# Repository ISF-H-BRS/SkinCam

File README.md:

# ISF SkinCam

## Introduction

The objective of the SkinCam project was to implement a camera system for real-time skin detection and face verification using multispectral short-wavelength infrared (SWIR) imaging. It originated from previous research projects carried out at Bonn-Rhein-Sieg University of Applied Sciences, such as [FeGeb](https://www.h-brs.de/de/fegeb) and [Beyond SPAI](https://www.h-brs.de/en/beyond-spai).

Based on the original concepts and designs, a new and improved system was developed, offering higher frame rates and optimized SWIR lighting. It is currently being used in various successor projects in biometrics research, such as [BIOLAB](https://www.h-brs.de/en/isf/biolab).

## Concept

The system is based on a Goldeye G-033 SWIR camera by Allied Vision, combined with a multispectral ring light operating at wavelengths of 1050, 1300 and 1550 nm. By evaluating the absorption ratios at these specific wavelengths, it is possible to identify those pixels which have properties characteristic of human skin using a pre-trained classifier.

## Software

The software developed as part of this project is based on code originally written for the project Beyond SPAI, which itself was based on the FeGeb project but extended the original concept by using three SWIR cameras simultaneously, using relay optics to split the image.

A number of image processing filters were implemented to compensate for imperfections in the relay optics. While these aren't strictly necessary for a single-camera system, they were retained in the SkinCam software anyway.

The implementation uses OpenCL for real-time image processing and skin classification and employs a number of other optimizations in order to achieve a stable frame rate of 40 Hz even on mid- to low-end systems.

In addition to the OpenCL [development headers](https://github.com/KhronosGroup/OpenCL-CLHPP), [Qt6](https://www.qt.io/product/qt6), [FreeImage](https://freeimage.sourceforge.io/), [libIFD](https://github.com/ISF-H-BRS/FaceDetector), [libusb](https://libusb.info/), [libzip](https://libzip.org/) and the [Vimba SDK](https://www.alliedvision.com/en/products/vimba-sdk/) are required to build and run the software. Since the Vimba terms and conditions do not permit end-users to download or use the software, the SkinCam software is by default compiled without support for the Vimba SDK.

The firmware directory contains project files for both the newly developed system, which is based on a STM32 microcontroller, as well as for the original FeGeb system, which was based on an 8-bit AVR microcontroller.

A number of captured test images are provided within the repository that can be used to evaluate the software without having the actual camera system available. A setup file is also provided, containing suitable settings as well as necessary calibration and classification data.

## License

All source code for the software and firmware is licensed under the terms of the GNU General Public License (GPLv3). All schematics, layout and CAD files are licensed under the terms of the Creative Commons Attribution-ShareAlike International Public License (CC BY-SA). See COPYING in the respective subdirectories for details.

## Further Information

This document will be expanded over time to further detail some of the underlying concepts. For the time being, detailed information on the original project and concepts can be found in Holger Steiner's PhD thesis, available online [here](http://www.grk1564.uni-siegen.de/publicationPDFbyID?ID=825).

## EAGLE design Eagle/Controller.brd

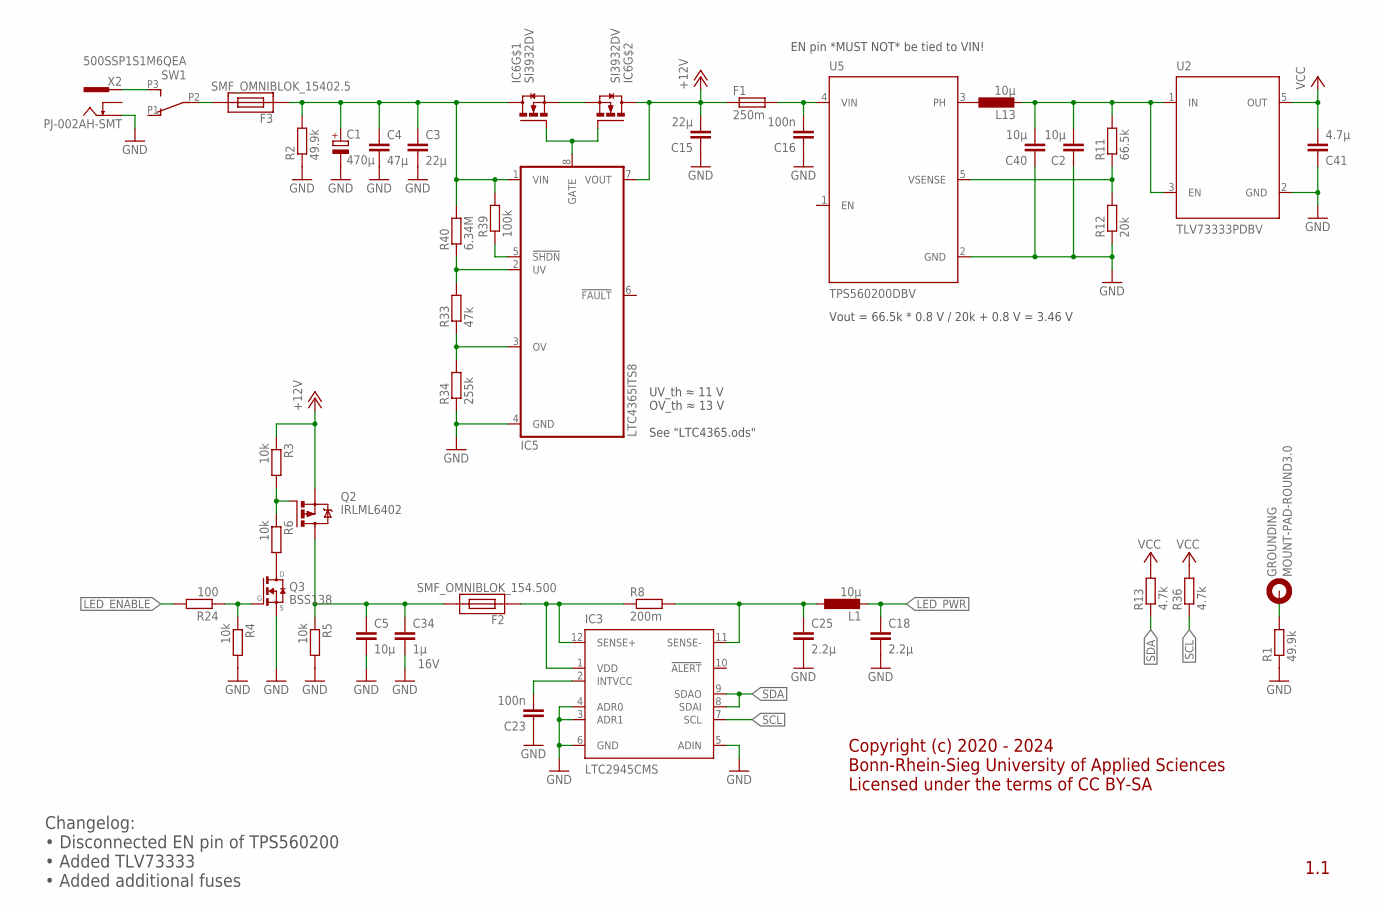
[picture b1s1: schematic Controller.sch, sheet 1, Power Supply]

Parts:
C1: 470µ; UD-10X10_NICHICON
C2, C5, C40: 10µ; C0805
C3: 22µ; C1206
C4: 47µ; C1206
C15: 22µ; C0805
C16, C23: 100n; C0603
C18, C25: 2.2µ; C0805
C34: 1µ; C0805; RATING 16V
C41: 4.7µ; C0805
F1: 250m; R0603
F2: SMF_OMNIBLOK_154.500; NANO2_SMF_FUSEBLOCK
F3: SMF_OMNIBLOK_15402.5; NANO2_SMF_FUSEBLOCK
GROUNDING: MOUNT-PAD-ROUND3.0; 3,0-PAD
IC3: LTC2945CMS; MSOP12
IC5: LTC4365ITS8; TSOT-23-8
IC6: SI3932DV; TSOT-23-6
L1: 10µ; SMD
L13: 10µ; 2SMD
Q2: IRLML6402; MICRO3
Q3: BSS138; SOT23
R1: 49.9k; R0805
R2: 49.9k; R1206
R3, R4, R6: 10k; R0603
R5: 10k; R1206
R8: 200m; R2512
R11: 66.5k; R0603
R12: 20k; R0603
R13, R36: 4.7k; R0603
R24: 100; R0603
R33: 47k; R0603
R34: 255k; R0603
R39: 100k; R0603
R40: 6.34M; R0603
SW1: 500SSP1S1M6QEA
U2: TLV73333PDBV; SOT-23
U5: TPS560200DBV; SOT-23
X2: PJ-002AH-SMT

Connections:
+12V: C15.2, F1.1, IC5.7 (VOUT), IC6.4 (D), Q2.2 (S), R3.1; also elsewhere on the board
GND: C1.-, C2.1, C3.2, C4.2, C5.2, C15.1, C16.1, C18.2, C23.1, C25.2, C34.2, C40.1, C41.1, IC3.3 (ADR1), IC3.4 (ADR0), IC3.5 (ADIN), IC3.6 (GND), IC5.4 (GND), Q3.2 (S), R1.1, R2.1, R4.2, R5.2, R12.1, R34.1, U2.2 (GND), U5.2 (GND), X2.2 (OUT); also elsewhere on the board
LED_ENABLE: R24.2; also elsewhere on the board
LED_PWR: C18.1, L1.2; also elsewhere on the board
unnamed: GROUNDING.B3,0, R1.2
unnamed: C2.2, C40.2, L13.P$2 (2), R11.2, U2.1 (IN), U2.3 (EN)
unnamed: C25.1, IC3.11 (SENSE-), L1.1, R8.2
unnamed: C16.2, F1.2, U5.4 (VIN)
unnamed: Q2.1 (G), R3.2, R6.1
unnamed: Q3.1 (G), R4.1, R24.1
unnamed: Q3.3 (D), R6.2
unnamed: C5.1, C34.1, F2.2, Q2.3 (D), R5.1
unnamed: SW1.P3 (3), X2.1-1 (IN), X2.1-2 (IN)
unnamed: L13.P$1 (1), U5.3 (PH)
unnamed: C1.+, C3.1, C4.1, F3.1, IC5.1 (VIN), IC6.6 (D), R2.2, R39.2, R40.2
unnamed: R11.1, R12.2, U5.5 (VSENSE)
unnamed: F2.1, IC3.1 (VDD), IC3.12 (SENSE+), R8.1
unnamed: F3.2, SW1.P2 (2)
unnamed: IC5.8 (GATE), IC6.1 (G), IC6.3 (G)
unnamed: IC5.3 (OV), R33.1, R34.2
unnamed: IC5.2 (UV), R33.2, R40.1
unnamed: IC5.5 (!SHDN), R39.1
unnamed: IC6.2 (S), IC6.5 (S)
unnamed: C23.2, IC3.2 (INTVCC)
SCL: IC3.7 (SCL), R36.1; also elsewhere on the board
SDA: IC3.8 (SDAI), IC3.9 (SDAO), R13.1; also elsewhere on the board
VCC: C41.2, R13.2, R36.2, U2.5 (OUT); also elsewhere on the board

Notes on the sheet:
Vout = 66.5k * 0.8 V / 20k + 0.8 V = 3.46 V
UV_th ≈ 11 V OV_th ≈ 13 V See "LTC4365.ods"
1.1
EN pin *MUST NOT* be tied to VIN!
Changelog: • Disconnected EN pin of TPS560200 • Added TLV73333 • Added additional fuses
Copyright (c) 2020 - 2024 Bonn-Rhein-Sieg University of Applied Sciences Licensed under the terms of CC BY-SA

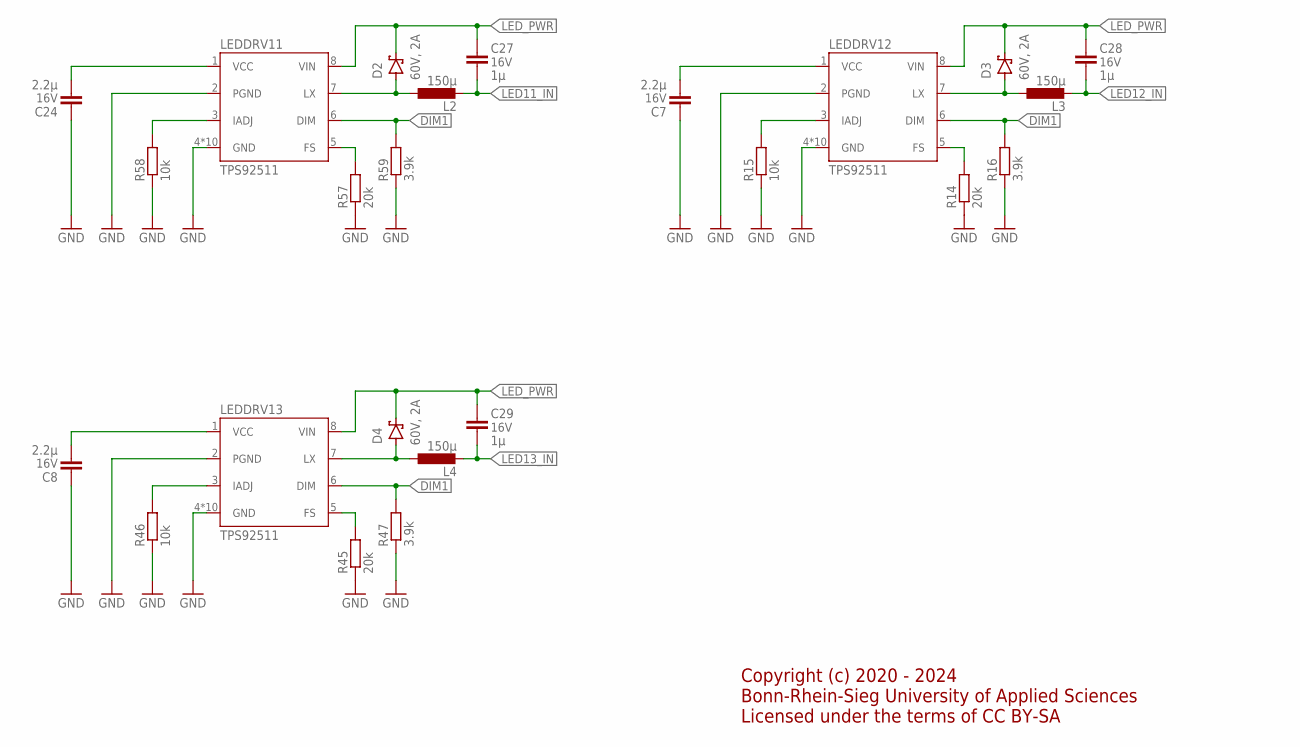
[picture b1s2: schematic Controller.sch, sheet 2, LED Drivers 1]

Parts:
C7, C8, C24: 2.2µ; C0603; RATING 16V
C27, C28, C29: 1µ; C0805; RATING 16V
D2, D3, D4: 60V, 2A; SMB
L2, L3, L4: 150µ; SMD
LEDDRV11, LEDDRV12, LEDDRV13: TPS92511; SOIC-8-EP
R14, R45, R57: 20k; R0603
R15, R46, R58: 10k; R0603
R16, R47, R59: 3.9k; R0603

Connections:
DIM1: LEDDRV11.6 (DIM), LEDDRV12.6 (DIM), LEDDRV13.6 (DIM), R16.2, R47.2, R59.2; also elsewhere on the board
GND: C7.1, C8.1, C24.1, LEDDRV11.2 (PGND), LEDDRV11.4 (GND), LEDDRV11.EPAD (GND), LEDDRV11.P$1 (GND), LEDDRV11.P$2 (GND), LEDDRV11.P$3 (GND), LEDDRV11.P$4 (GND), LEDDRV11.P$5 (GND), LEDDRV11.P$6 (GND), LEDDRV11.P$7 (GND), LEDDRV11.P$8 (GND), LEDDRV12.2 (PGND), LEDDRV12.4 (GND), LEDDRV12.EPAD (GND), LEDDRV12.P$1 (GND), LEDDRV12.P$2 (GND), LEDDRV12.P$3 (GND), LEDDRV12.P$4 (GND), LEDDRV12.P$5 (GND), LEDDRV12.P$6 (GND), LEDDRV12.P$7 (GND), LEDDRV12.P$8 (GND), LEDDRV13.2 (PGND), LEDDRV13.4 (GND), LEDDRV13.EPAD (GND), LEDDRV13.P$1 (GND), LEDDRV13.P$2 (GND), LEDDRV13.P$3 (GND), LEDDRV13.P$4 (GND), LEDDRV13.P$5 (GND), LEDDRV13.P$6 (GND), LEDDRV13.P$7 (GND), LEDDRV13.P$8 (GND), R14.1, R15.1, R16.1, R45.1, R46.1, R47.1, R57.1, R58.1, R59.1; also elsewhere on the board
LED11_IN: C27.2, L2.2; also elsewhere on the board
LED12_IN: C28.2, L3.2; also elsewhere on the board
LED13_IN: C29.2, L4.2; also elsewhere on the board
LED_PWR: C27.1, C28.1, C29.1, D2.C, D3.C, D4.C, LEDDRV11.8 (VIN), LEDDRV12.8 (VIN), LEDDRV13.8 (VIN); also elsewhere on the board
unnamed: D3.A, L3.1, LEDDRV12.7 (LX)
unnamed: LEDDRV12.5 (FS), R14.2
unnamed: LEDDRV12.3 (IADJ), R15.2
unnamed: C7.2, LEDDRV12.1 (VCC)
unnamed: D4.A, L4.1, LEDDRV13.7 (LX)
unnamed: LEDDRV13.5 (FS), R45.2
unnamed: LEDDRV13.3 (IADJ), R46.2
unnamed: C8.2, LEDDRV13.1 (VCC)
unnamed: D2.A, L2.1, LEDDRV11.7 (LX)
unnamed: LEDDRV11.5 (FS), R57.2
unnamed: LEDDRV11.3 (IADJ), R58.2
unnamed: C24.2, LEDDRV11.1 (VCC)

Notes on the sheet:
Copyright (c) 2020 - 2024 Bonn-Rhein-Sieg University of Applied Sciences Licensed under the terms of CC BY-SA

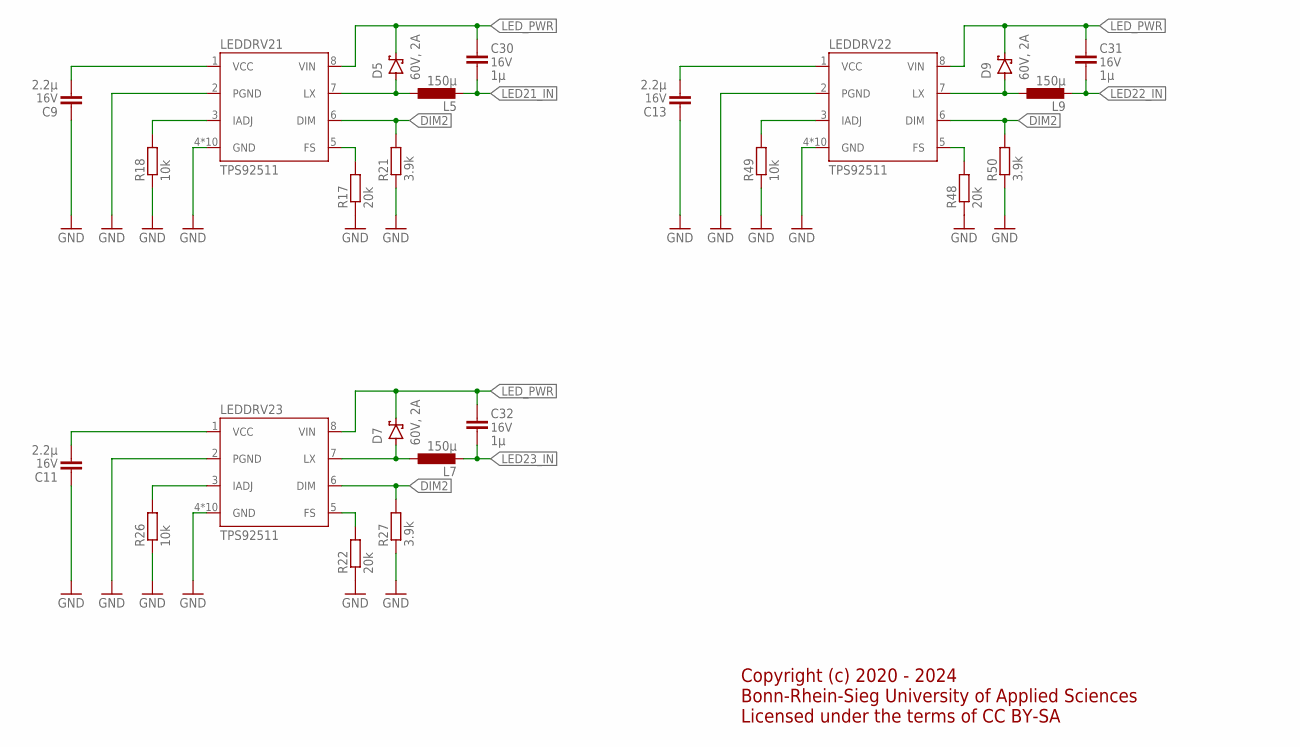
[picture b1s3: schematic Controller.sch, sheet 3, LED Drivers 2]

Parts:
C9, C11, C13: 2.2µ; C0603; RATING 16V
C30, C31, C32: 1µ; C0805; RATING 16V
D5, D7, D9: 60V, 2A; SMB
L5, L7, L9: 150µ; SMD
LEDDRV21, LEDDRV22, LEDDRV23: TPS92511; SOIC-8-EP
R17, R22, R48: 20k; R0603
R18, R26, R49: 10k; R0603
R21, R27, R50: 3.9k; R0603

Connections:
DIM2: LEDDRV21.6 (DIM), LEDDRV22.6 (DIM), LEDDRV23.6 (DIM), R21.2, R27.2, R50.2; also elsewhere on the board
GND: C9.1, C11.1, C13.1, LEDDRV21.2 (PGND), LEDDRV21.4 (GND), LEDDRV21.EPAD (GND), LEDDRV21.P$1 (GND), LEDDRV21.P$2 (GND), LEDDRV21.P$3 (GND), LEDDRV21.P$4 (GND), LEDDRV21.P$5 (GND), LEDDRV21.P$6 (GND), LEDDRV21.P$7 (GND), LEDDRV21.P$8 (GND), LEDDRV22.2 (PGND), LEDDRV22.4 (GND), LEDDRV22.EPAD (GND), LEDDRV22.P$1 (GND), LEDDRV22.P$2 (GND), LEDDRV22.P$3 (GND), LEDDRV22.P$4 (GND), LEDDRV22.P$5 (GND), LEDDRV22.P$6 (GND), LEDDRV22.P$7 (GND), LEDDRV22.P$8 (GND), LEDDRV23.2 (PGND), LEDDRV23.4 (GND), LEDDRV23.EPAD (GND), LEDDRV23.P$1 (GND), LEDDRV23.P$2 (GND), LEDDRV23.P$3 (GND), LEDDRV23.P$4 (GND), LEDDRV23.P$5 (GND), LEDDRV23.P$6 (GND), LEDDRV23.P$7 (GND), LEDDRV23.P$8 (GND), R17.1, R18.1, R21.1, R22.1, R26.1, R27.1, R48.1, R49.1, R50.1; also elsewhere on the board
LED21_IN: C30.2, L5.2; also elsewhere on the board
LED22_IN: C31.2, L9.2; also elsewhere on the board
LED23_IN: C32.2, L7.2; also elsewhere on the board
LED_PWR: C30.1, C31.1, C32.1, D5.C, D7.C, D9.C, LEDDRV21.8 (VIN), LEDDRV22.8 (VIN), LEDDRV23.8 (VIN); also elsewhere on the board
unnamed: D5.A, L5.1, LEDDRV21.7 (LX)
unnamed: LEDDRV21.5 (FS), R17.2
unnamed: LEDDRV21.3 (IADJ), R18.2
unnamed: C9.2, LEDDRV21.1 (VCC)
unnamed: D7.A, L7.1, LEDDRV23.7 (LX)
unnamed: LEDDRV23.5 (FS), R22.2
unnamed: LEDDRV23.3 (IADJ), R26.2
unnamed: C11.2, LEDDRV23.1 (VCC)
unnamed: D9.A, L9.1, LEDDRV22.7 (LX)
unnamed: LEDDRV22.5 (FS), R48.2
unnamed: LEDDRV22.3 (IADJ), R49.2
unnamed: C13.2, LEDDRV22.1 (VCC)

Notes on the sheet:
Copyright (c) 2020 - 2024 Bonn-Rhein-Sieg University of Applied Sciences Licensed under the terms of CC BY-SA

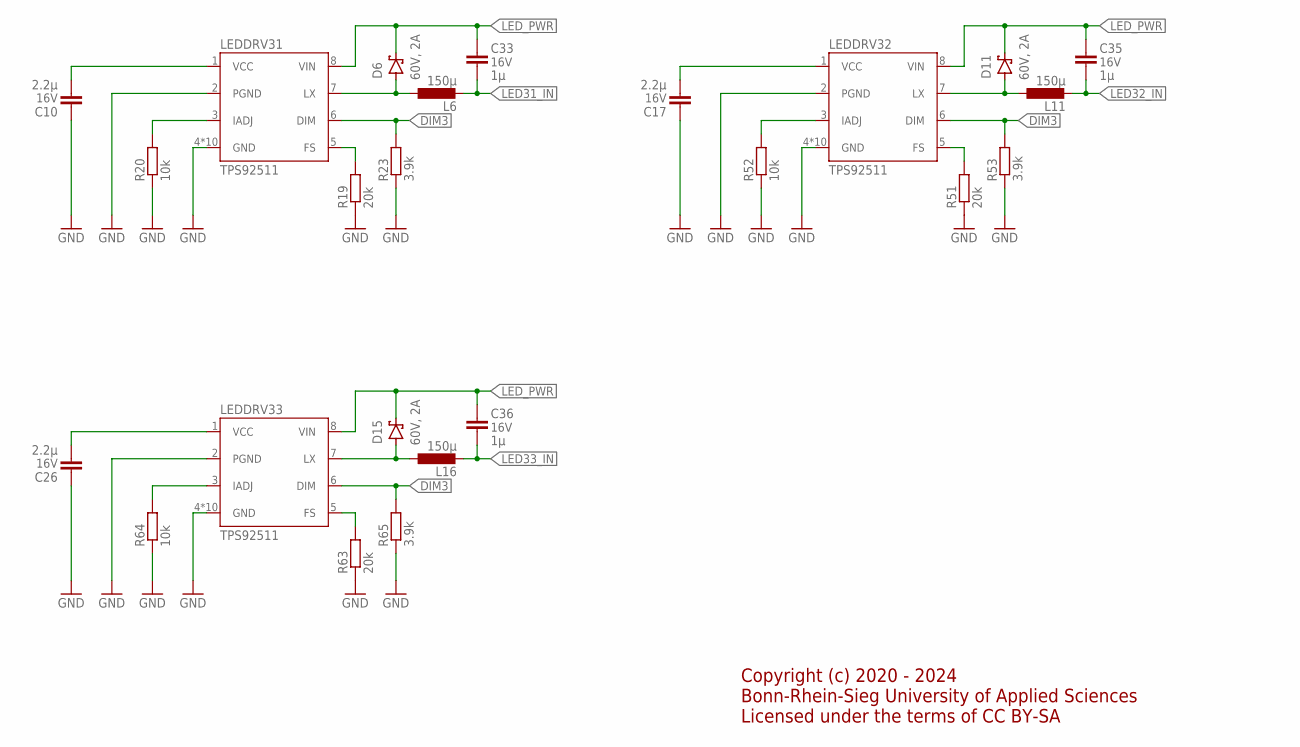
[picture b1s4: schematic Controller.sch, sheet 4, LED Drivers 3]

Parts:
C10, C17, C26: 2.2µ; C0603; RATING 16V
C33, C35, C36: 1µ; C0805; RATING 16V
D6, D11, D15: 60V, 2A; SMB
L6, L11, L16: 150µ; SMD
LEDDRV31, LEDDRV32, LEDDRV33: TPS92511; SOIC-8-EP
R19, R51, R63: 20k; R0603
R20, R52, R64: 10k; R0603
R23, R53, R65: 3.9k; R0603

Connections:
DIM3: LEDDRV31.6 (DIM), LEDDRV32.6 (DIM), LEDDRV33.6 (DIM), R23.2, R53.2, R65.2; also elsewhere on the board
GND: C10.1, C17.1, C26.1, LEDDRV31.2 (PGND), LEDDRV31.4 (GND), LEDDRV31.EPAD (GND), LEDDRV31.P$1 (GND), LEDDRV31.P$2 (GND), LEDDRV31.P$3 (GND), LEDDRV31.P$4 (GND), LEDDRV31.P$5 (GND), LEDDRV31.P$6 (GND), LEDDRV31.P$7 (GND), LEDDRV31.P$8 (GND), LEDDRV32.2 (PGND), LEDDRV32.4 (GND), LEDDRV32.EPAD (GND), LEDDRV32.P$1 (GND), LEDDRV32.P$2 (GND), LEDDRV32.P$3 (GND), LEDDRV32.P$4 (GND), LEDDRV32.P$5 (GND), LEDDRV32.P$6 (GND), LEDDRV32.P$7 (GND), LEDDRV32.P$8 (GND), LEDDRV33.2 (PGND), LEDDRV33.4 (GND), LEDDRV33.EPAD (GND), LEDDRV33.P$1 (GND), LEDDRV33.P$2 (GND), LEDDRV33.P$3 (GND), LEDDRV33.P$4 (GND), LEDDRV33.P$5 (GND), LEDDRV33.P$6 (GND), LEDDRV33.P$7 (GND), LEDDRV33.P$8 (GND), R19.1, R20.1, R23.1, R51.1, R52.1, R53.1, R63.1, R64.1, R65.1; also elsewhere on the board
LED31_IN: C33.2, L6.2; also elsewhere on the board
LED32_IN: C35.2, L11.2; also elsewhere on the board
LED33_IN: C36.2, L16.2; also elsewhere on the board
LED_PWR: C33.1, C35.1, C36.1, D6.C, D11.C, D15.C, LEDDRV31.8 (VIN), LEDDRV32.8 (VIN), LEDDRV33.8 (VIN); also elsewhere on the board
unnamed: D6.A, L6.1, LEDDRV31.7 (LX)
unnamed: LEDDRV31.5 (FS), R19.2
unnamed: LEDDRV31.3 (IADJ), R20.2
unnamed: C10.2, LEDDRV31.1 (VCC)
unnamed: D11.A, L11.1, LEDDRV32.7 (LX)
unnamed: LEDDRV32.5 (FS), R51.2
unnamed: LEDDRV32.3 (IADJ), R52.2
unnamed: C17.2, LEDDRV32.1 (VCC)
unnamed: D15.A, L16.1, LEDDRV33.7 (LX)
unnamed: LEDDRV33.5 (FS), R63.2
unnamed: LEDDRV33.3 (IADJ), R64.2
unnamed: C26.2, LEDDRV33.1 (VCC)

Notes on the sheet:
Copyright (c) 2020 - 2024 Bonn-Rhein-Sieg University of Applied Sciences Licensed under the terms of CC BY-SA

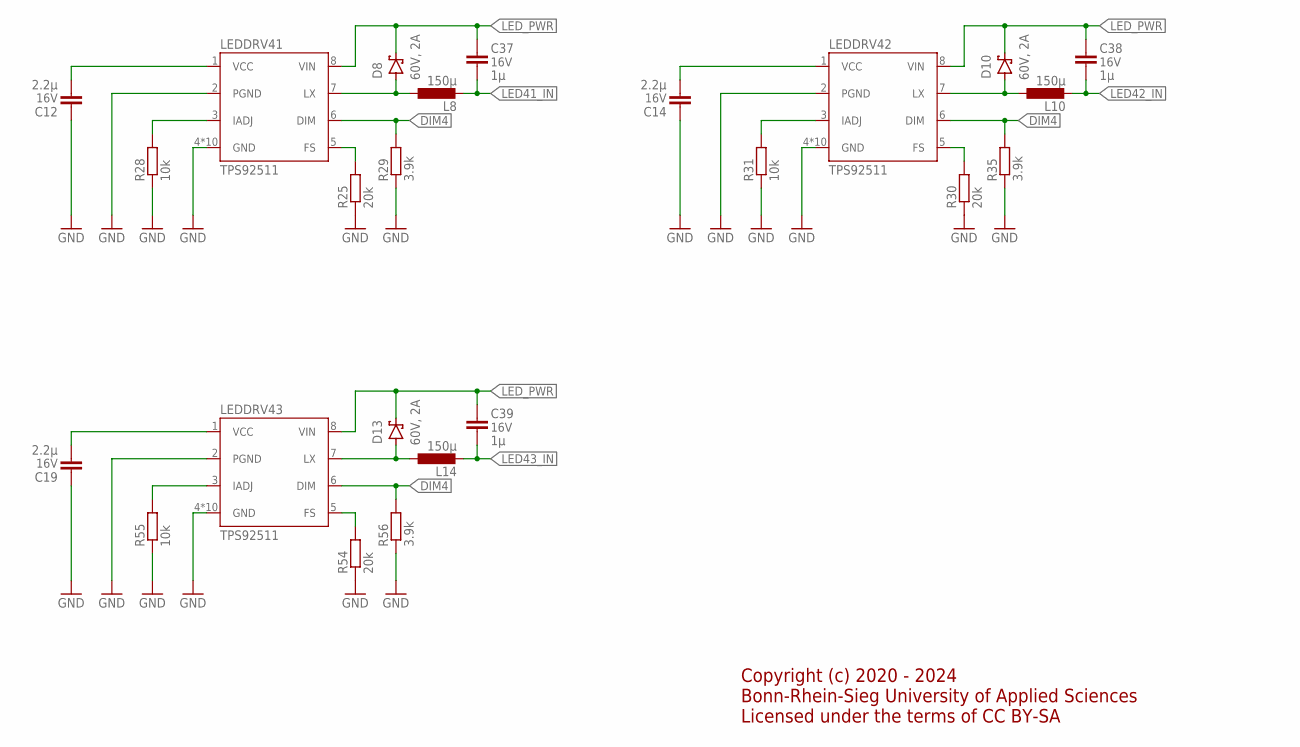
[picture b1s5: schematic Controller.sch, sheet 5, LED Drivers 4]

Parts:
C12, C14, C19: 2.2µ; C0603; RATING 16V
C37, C38, C39: 1µ; C0805; RATING 16V
D8, D10, D13: 60V, 2A; SMB
L8, L10, L14: 150µ; SMD
LEDDRV41, LEDDRV42, LEDDRV43: TPS92511; SOIC-8-EP
R25, R30, R54: 20k; R0603
R28, R31, R55: 10k; R0603
R29, R35, R56: 3.9k; R0603

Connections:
DIM4: LEDDRV41.6 (DIM), LEDDRV42.6 (DIM), LEDDRV43.6 (DIM), R29.2, R35.2, R56.2; also elsewhere on the board
GND: C12.1, C14.1, C19.1, LEDDRV41.2 (PGND), LEDDRV41.4 (GND), LEDDRV41.EPAD (GND), LEDDRV41.P$1 (GND), LEDDRV41.P$2 (GND), LEDDRV41.P$3 (GND), LEDDRV41.P$4 (GND), LEDDRV41.P$5 (GND), LEDDRV41.P$6 (GND), LEDDRV41.P$7 (GND), LEDDRV41.P$8 (GND), LEDDRV42.2 (PGND), LEDDRV42.4 (GND), LEDDRV42.EPAD (GND), LEDDRV42.P$1 (GND), LEDDRV42.P$2 (GND), LEDDRV42.P$3 (GND), LEDDRV42.P$4 (GND), LEDDRV42.P$5 (GND), LEDDRV42.P$6 (GND), LEDDRV42.P$7 (GND), LEDDRV42.P$8 (GND), LEDDRV43.2 (PGND), LEDDRV43.4 (GND), LEDDRV43.EPAD (GND), LEDDRV43.P$1 (GND), LEDDRV43.P$2 (GND), LEDDRV43.P$3 (GND), LEDDRV43.P$4 (GND), LEDDRV43.P$5 (GND), LEDDRV43.P$6 (GND), LEDDRV43.P$7 (GND), LEDDRV43.P$8 (GND), R25.1, R28.1, R29.1, R30.1, R31.1, R35.1, R54.1, R55.1, R56.1; also elsewhere on the board
LED41_IN: C37.2, L8.2; also elsewhere on the board
LED42_IN: C38.2, L10.2; also elsewhere on the board
LED43_IN: C39.2, L14.2; also elsewhere on the board
LED_PWR: C37.1, C38.1, C39.1, D8.C, D10.C, D13.C, LEDDRV41.8 (VIN), LEDDRV42.8 (VIN), LEDDRV43.8 (VIN); also elsewhere on the board
unnamed: D8.A, L8.1, LEDDRV41.7 (LX)
unnamed: LEDDRV41.5 (FS), R25.2
unnamed: LEDDRV41.3 (IADJ), R28.2
unnamed: C12.2, LEDDRV41.1 (VCC)
unnamed: D10.A, L10.1, LEDDRV42.7 (LX)
unnamed: LEDDRV42.5 (FS), R30.2
unnamed: LEDDRV42.3 (IADJ), R31.2
unnamed: C14.2, LEDDRV42.1 (VCC)
unnamed: D13.A, L14.1, LEDDRV43.7 (LX)
unnamed: LEDDRV43.5 (FS), R54.2
unnamed: LEDDRV43.3 (IADJ), R55.2
unnamed: C19.2, LEDDRV43.1 (VCC)

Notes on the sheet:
Copyright (c) 2020 - 2024 Bonn-Rhein-Sieg University of Applied Sciences Licensed under the terms of CC BY-SA

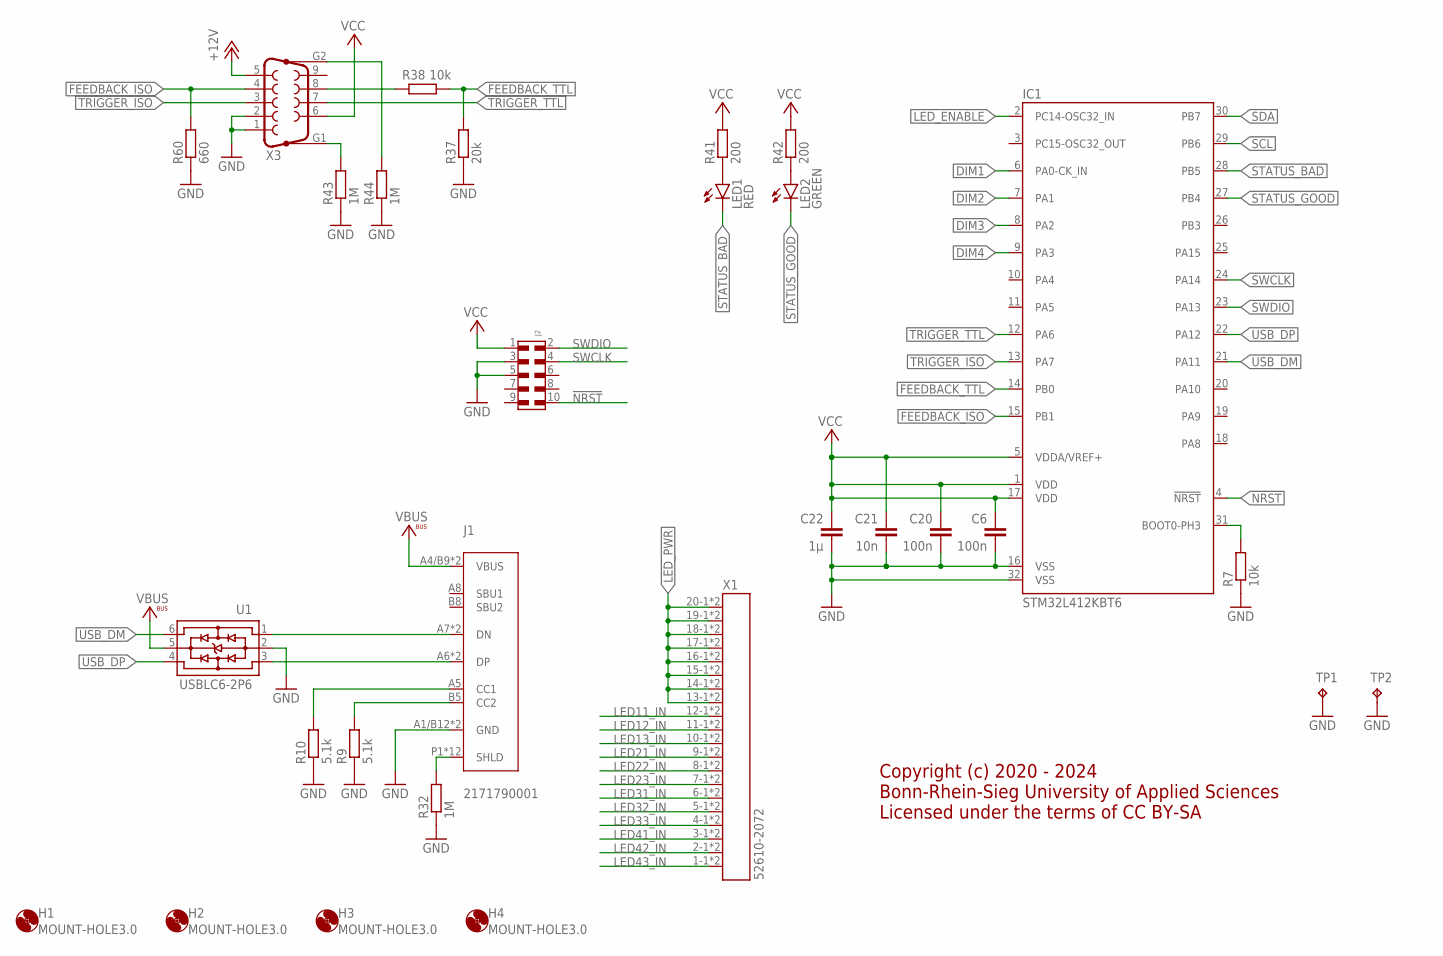
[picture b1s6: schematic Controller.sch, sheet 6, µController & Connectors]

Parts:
C6, C20: 100n; C0603
C21: 10n; C0603
C22: 1µ; C0603
H1, H2, H3, H4: MOUNT-HOLE3.0; 3,0
IC1: STM32L412KBT6; LQFP32
J1: 2171790001; 2171790001_MOL
J2: 6210XX21021_62101021021; 62101021021
LED1: RED; LED3MM
LED2: GREEN; LED3MM
R7, R38: 10k; R0603
R9, R10: 5.1k; R0603
R32, R43, R44: 1M; R0603
R37: 20k; R0603
R41, R42: 200; R0603
R60: 660; R0603
TP1, TP2: TP3.8X2.03; 3.8X2.03
U1: USBLC6-2P6; SOT-666
X1: 52610-2072
X3: F09HP

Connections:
!NRST: IC1.4 (!NRST), J2.10
+12V: X3.5; also elsewhere on the board
DIM1: IC1.6 (PA0-CK_IN); also elsewhere on the board
DIM2: IC1.7 (PA1); also elsewhere on the board
DIM3: IC1.8 (PA2); also elsewhere on the board
DIM4: IC1.9 (PA3); also elsewhere on the board
FEEDBACK_ISO: IC1.15 (PB1), R60.2, X3.4
FEEDBACK_TTL: IC1.14 (PB0), R37.2, R38.1
GND: C6.2, C20.2, C21.2, C22.2, IC1.16 (VSS), IC1.32 (VSS), J1.A1/B12 (GND), J1.B1/A12 (GND), J2.3, J2.5, R7.1, R9.1, R10.1, R32.1, R37.1, R43.1, R44.1, R60.1, TP1.TP, TP2.TP, U1.2, X3.1, X3.2; also elsewhere on the board
LED11_IN: X1.12-1 (12), X1.12-2 (12); also elsewhere on the board
LED12_IN: X1.11-1 (11), X1.11-2 (11); also elsewhere on the board
LED13_IN: X1.10-1 (10), X1.10-2 (10); also elsewhere on the board
LED21_IN: X1.9-1 (9), X1.9-2 (9); also elsewhere on the board
LED22_IN: X1.8-1 (8), X1.8-2 (8); also elsewhere on the board
LED23_IN: X1.7-1 (7), X1.7-2 (7); also elsewhere on the board
LED31_IN: X1.6-1 (6), X1.6-2 (6); also elsewhere on the board
LED32_IN: X1.5-1 (5), X1.5-2 (5); also elsewhere on the board
LED33_IN: X1.4-1 (4), X1.4-2 (4); also elsewhere on the board
LED41_IN: X1.3-1 (3), X1.3-2 (3); also elsewhere on the board
LED42_IN: X1.2-1 (2), X1.2-2 (2); also elsewhere on the board
LED43_IN: X1.1-1 (1), X1.1-2 (1); also elsewhere on the board
LED_ENABLE: IC1.2 (PC14-OSC32_IN); also elsewhere on the board
LED_PWR: X1.13-1 (13), X1.13-2 (13), X1.14-1 (14), X1.14-2 (14), X1.15-1 (15), X1.15-2 (15), X1.16-1 (16), X1.16-2 (16), X1.17-1 (17), X1.17-2 (17), X1.18-1 (18), X1.18-2 (18), X1.19-1 (19), X1.19-2 (19), X1.20-1 (20), X1.20-2 (20); also elsewhere on the board
unnamed: IC1.31 (BOOT0-PH3), R7.2
unnamed: R43.2, X3.G1
unnamed: J1.A7 (DN), J1.B7 (DN), U1.1
unnamed: J1.A6 (DP), J1.B6 (DP), U1.3
unnamed: J1.B5 (CC2), R9.2
unnamed: J1.A5 (CC1), R10.2
unnamed: J1.P1 (SHLD), J1.P2 (SHLD), J1.P3 (SHLD), J1.P4 (SHLD), J1.S1 (SHLD), J1.S2 (SHLD), J1.S3 (SHLD), J1.S4 (SHLD), J1.S5 (SHLD), J1.S6 (SHLD), J1.S7 (SHLD), J1.S8 (SHLD), R32.2
unnamed: R38.2, X3.8
unnamed: LED1.A, R41.1
unnamed: LED2.A, R42.1
unnamed: R44.2, X3.G2
SCL: IC1.29 (PB6); also elsewhere on the board
SDA: IC1.30 (PB7); also elsewhere on the board
STATUS_BAD: IC1.28 (PB5), LED1.K (C)
STATUS_GOOD: IC1.27 (PB4), LED2.K (C)
SWCLK: IC1.24 (PA14), J2.4
SWDIO: IC1.23 (PA13), J2.2
TRIGGER_ISO: IC1.13 (PA7), X3.3
TRIGGER_TTL: IC1.12 (PA6), X3.7
USB_DM: IC1.21 (PA11), U1.6
USB_DP: IC1.22 (PA12), U1.4
VBUS: J1.A4/B9 (VBUS), J1.B4/A9 (VBUS), U1.5
VCC: C6.1, C20.1, C21.1, C22.1, IC1.1 (VDD), IC1.5 (VDDA/VREF+), IC1.17 (VDD), J2.1, R41.2, R42.2, X3.6; also elsewhere on the board

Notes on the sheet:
Copyright (c) 2020 - 2024 Bonn-Rhein-Sieg University of Applied Sciences Licensed under the terms of CC BY-SA

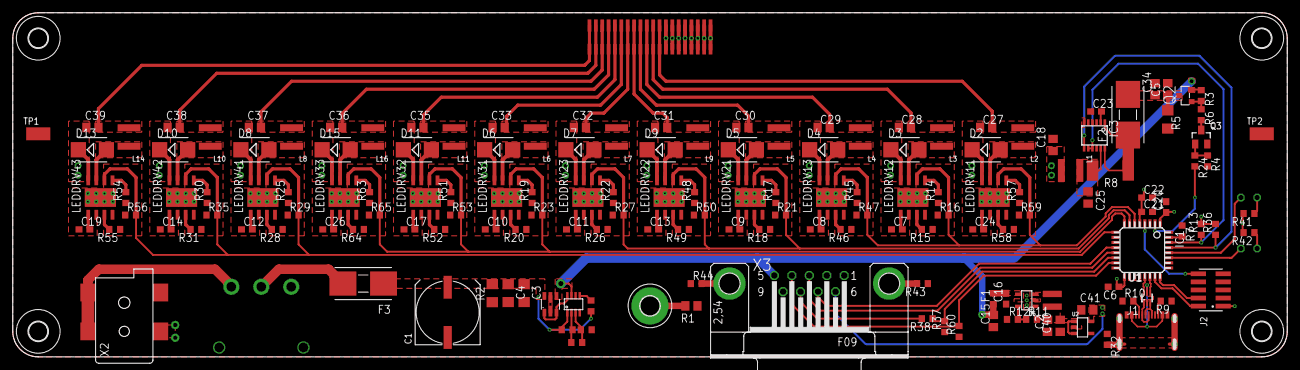
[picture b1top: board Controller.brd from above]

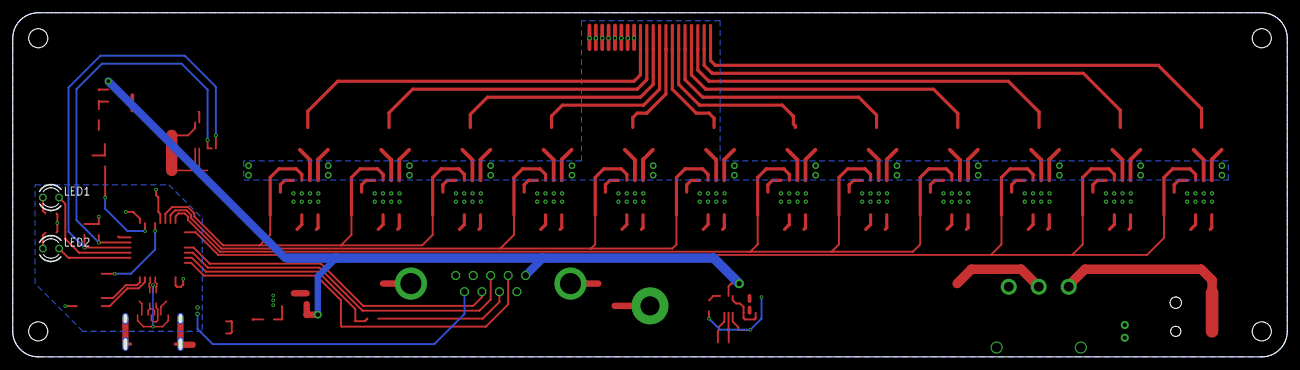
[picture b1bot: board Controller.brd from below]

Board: 2 copper layers, 199.4 x 53.4 mm, 169 parts (2 on the bottom side), 114 nets.

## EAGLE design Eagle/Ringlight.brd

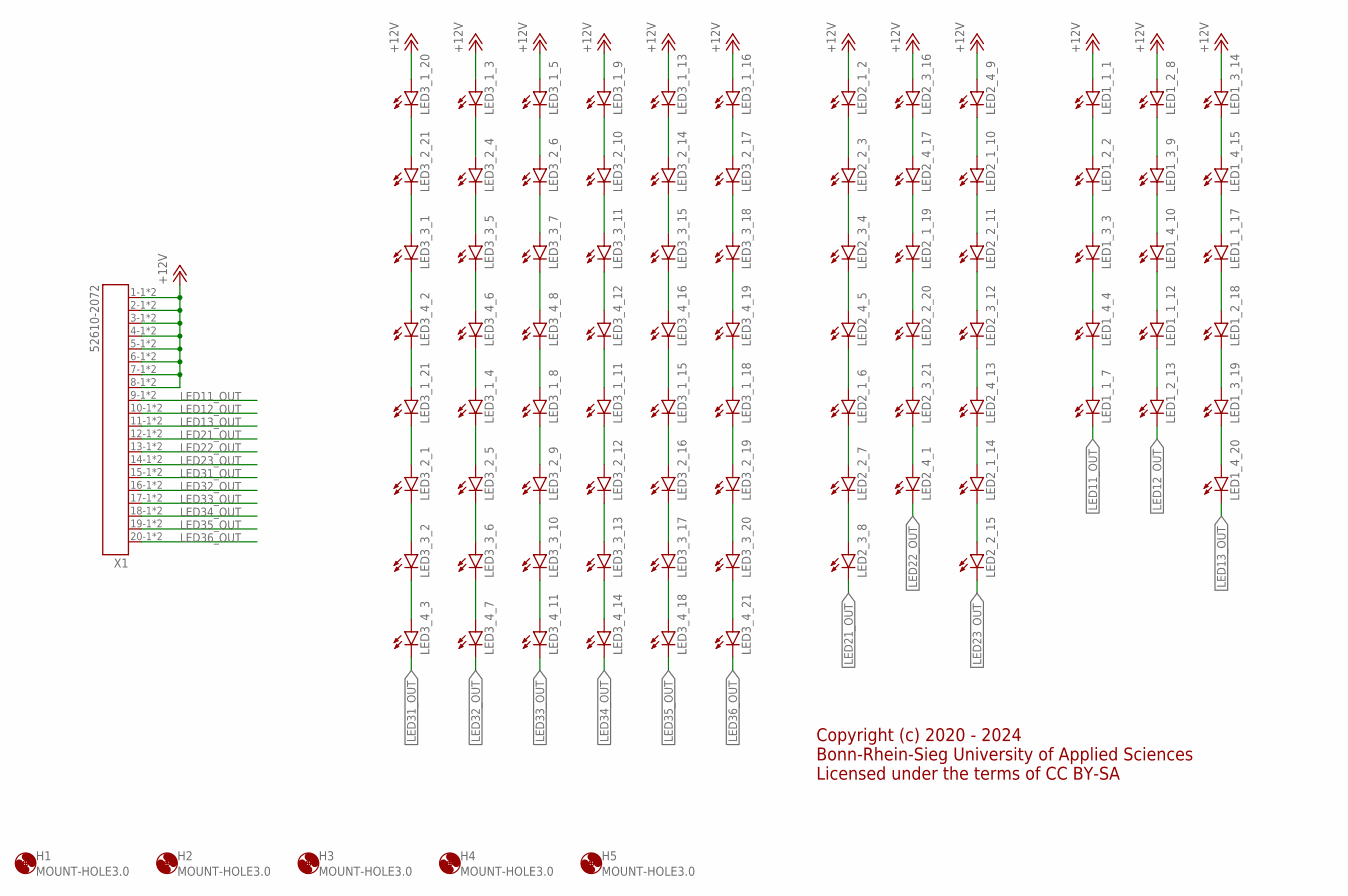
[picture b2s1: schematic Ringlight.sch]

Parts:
H1, H2, H3, H4, H5: MOUNT-HOLE3.0; 3,0
LED1_1_1, LED1_1_7, LED1_1_12, LED1_1_17, LED1_2_2, LED1_2_8, LED1_2_13, LED1_2_18, LED1_3_3, LED1_3_9, LED1_3_14, LED1_3_19, LED1_4_4, LED1_4_10, LED1_4_15, LED1_4_20, LED2_1_2, LED2_1_6, LED2_1_10, LED2_1_14, LED2_1_19, LED2_2_3, LED2_2_7, LED2_2_11, LED2_2_15, LED2_2_20, LED2_3_4, LED2_3_8, LED2_3_12, LED2_3_16, LED2_3_21, LED2_4_1, LED2_4_5, LED2_4_9, LED2_4_13, LED2_4_17, LED3_1_3, LED3_1_4, LED3_1_5, LED3_1_8, LED3_1_9, LED3_1_11, LED3_1_13, LED3_1_15, LED3_1_16, LED3_1_18, LED3_1_20, LED3_1_21, LED3_2_1, LED3_2_4, LED3_2_5, LED3_2_6, LED3_2_9, LED3_2_10, LED3_2_12, LED3_2_14, LED3_2_16, LED3_2_17, LED3_2_19, LED3_2_21, LED3_3_1, LED3_3_2, LED3_3_5, LED3_3_6, LED3_3_7, LED3_3_10, LED3_3_11, LED3_3_13, LED3_3_15, LED3_3_17, LED3_3_18, LED3_3_20, LED3_4_2, LED3_4_3, LED3_4_6, LED3_4_7, LED3_4_8, LED3_4_11, LED3_4_12, LED3_4_14, LED3_4_16, LED3_4_18, LED3_4_19, LED3_4_21: LED5MM
X1: 52610-2072

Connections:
+12V: LED1_1_1.A, LED1_2_8.A, LED1_3_14.A, LED2_1_2.A, LED2_3_16.A, LED2_4_9.A, LED3_1_3.A, LED3_1_5.A, LED3_1_9.A, LED3_1_13.A, LED3_1_16.A, LED3_1_20.A, X1.1-1 (1), X1.1-2 (1), X1.2-1 (2), X1.2-2 (2), X1.3-1 (3), X1.3-2 (3), X1.4-1 (4), X1.4-2 (4), X1.5-1 (5), X1.5-2 (5), X1.6-1 (6), X1.6-2 (6), X1.7-1 (7), X1.7-2 (7), X1.8-1 (8), X1.8-2 (8)
LED11_OUT: LED1_1_7.K (C), X1.9-1 (9), X1.9-2 (9)
LED12_OUT: LED1_2_13.K (C), X1.10-1 (10), X1.10-2 (10)
LED13_OUT: LED1_4_20.K (C), X1.11-1 (11), X1.11-2 (11)
LED21_OUT: LED2_3_8.K (C), X1.12-1 (12), X1.12-2 (12)
LED22_OUT: LED2_4_1.K (C), X1.13-1 (13), X1.13-2 (13)
LED23_OUT: LED2_2_15.K (C), X1.14-1 (14), X1.14-2 (14)
LED31_OUT: LED3_4_3.K (C), X1.15-1 (15), X1.15-2 (15)
LED32_OUT: LED3_4_7.K (C), X1.16-1 (16), X1.16-2 (16)
LED33_OUT: LED3_4_11.K (C), X1.17-1 (17), X1.17-2 (17)
LED34_OUT: LED3_4_14.K (C), X1.18-1 (18), X1.18-2 (18)
LED35_OUT: LED3_4_18.K (C), X1.19-1 (19), X1.19-2 (19)
LED36_OUT: LED3_4_21.K (C), X1.20-1 (20), X1.20-2 (20)
unnamed: LED1_1_1.K (C), LED1_2_2.A
unnamed: LED1_2_2.K (C), LED1_3_3.A
unnamed: LED1_3_3.K (C), LED1_4_4.A
unnamed: LED1_1_12.A, LED1_4_10.K (C)
unnamed: LED1_2_8.K (C), LED1_3_9.A
unnamed: LED1_3_9.K (C), LED1_4_10.A
unnamed: LED1_1_17.A, LED1_4_15.K (C)
unnamed: LED1_1_12.K (C), LED1_2_13.A
unnamed: LED1_3_14.K (C), LED1_4_15.A
unnamed: LED2_2_11.K (C), LED2_3_12.A
unnamed: LED1_1_17.K (C), LED1_2_18.A
unnamed: LED1_2_18.K (C), LED1_3_19.A
unnamed: LED1_3_19.K (C), LED1_4_20.A
unnamed: LED2_1_2.K (C), LED2_2_3.A
unnamed: LED2_2_3.K (C), LED2_3_4.A
unnamed: LED2_3_4.K (C), LED2_4_5.A
unnamed: LED2_1_6.A, LED2_4_5.K (C)
unnamed: LED2_3_16.K (C), LED2_4_17.A
unnamed: LED2_2_7.K (C), LED2_3_8.A
unnamed: LED2_1_10.A, LED2_4_9.K (C)
unnamed: LED2_1_10.K (C), LED2_2_11.A
unnamed: LED3_1_3.K (C), LED3_2_4.A
unnamed: LED2_3_12.K (C), LED2_4_13.A
unnamed: LED2_1_14.A, LED2_4_13.K (C)
unnamed: LED2_1_14.K (C), LED2_2_15.A
unnamed: LED3_2_4.K (C), LED3_3_5.A
unnamed: LED2_1_19.A, LED2_4_17.K (C)
unnamed: LED2_1_19.K (C), LED2_2_20.A
unnamed: LED2_2_20.K (C), LED2_3_21.A
unnamed: LED2_3_21.K (C), LED2_4_1.A
unnamed: LED3_3_5.K (C), LED3_4_6.A
unnamed: LED3_1_4.A, LED3_4_6.K (C)
unnamed: LED3_1_4.K (C), LED3_2_5.A
unnamed: LED3_2_5.K (C), LED3_3_6.A
unnamed: LED3_3_6.K (C), LED3_4_7.A
unnamed: LED3_1_5.K (C), LED3_2_6.A
unnamed: LED3_2_6.K (C), LED3_3_7.A
unnamed: LED3_3_7.K (C), LED3_4_8.A
unnamed: LED3_1_8.A, LED3_4_8.K (C)
unnamed: LED3_1_8.K (C), LED3_2_9.A
unnamed: LED3_2_9.K (C), LED3_3_10.A
unnamed: LED3_3_10.K (C), LED3_4_11.A
unnamed: LED3_1_9.K (C), LED3_2_10.A
unnamed: LED3_2_10.K (C), LED3_3_11.A
unnamed: LED3_3_11.K (C), LED3_4_12.A
unnamed: LED3_1_11.A, LED3_4_12.K (C)
unnamed: LED3_1_11.K (C), LED3_2_12.A
unnamed: LED3_2_12.K (C), LED3_3_13.A
unnamed: LED3_3_13.K (C), LED3_4_14.A
unnamed: LED3_1_13.K (C), LED3_2_14.A
unnamed: LED3_2_14.K (C), LED3_3_15.A
unnamed: LED3_3_15.K (C), LED3_4_16.A
unnamed: LED3_1_15.A, LED3_4_16.K (C)
unnamed: LED3_1_15.K (C), LED3_2_16.A
unnamed: LED3_2_16.K (C), LED3_3_17.A
unnamed: LED3_3_17.K (C), LED3_4_18.A
unnamed: LED3_1_16.K (C), LED3_2_17.A
unnamed: LED3_2_17.K (C), LED3_3_18.A
unnamed: LED3_3_18.K (C), LED3_4_19.A
unnamed: LED3_1_18.A, LED3_4_19.K (C)
unnamed: LED3_1_18.K (C), LED3_2_19.A
unnamed: LED3_2_19.K (C), LED3_3_20.A
unnamed: LED3_3_20.K (C), LED3_4_21.A
unnamed: LED3_1_20.K (C), LED3_2_21.A
unnamed: LED3_2_21.K (C), LED3_3_1.A
unnamed: LED3_3_1.K (C), LED3_4_2.A
unnamed: LED3_1_21.A, LED3_4_2.K (C)
unnamed: LED3_1_21.K (C), LED3_2_1.A
unnamed: LED3_2_1.K (C), LED3_3_2.A
unnamed: LED3_3_2.K (C), LED3_4_3.A
unnamed: LED1_1_7.A, LED1_4_4.K (C)
unnamed: LED2_1_6.K (C), LED2_2_7.A

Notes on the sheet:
Copyright (c) 2020 - 2024 Bonn-Rhein-Sieg University of Applied Sciences Licensed under the terms of CC BY-SA

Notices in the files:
parts and their libraries:
WR-PHD: Copyright: Würth Elektronik
COPYRIGHT: Copyright (C) 2021 Ultra Librarian. All rights reserved.
